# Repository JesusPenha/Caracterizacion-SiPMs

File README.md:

Este repositorio contiene los archivos y los codigos utilizados para la caracterización de los fotomultiplicadores de silicio S133601350CS de hamamatsu.

-La carpeta FotonEquivalente contiene los codigos para el cálculo del equivalente en voltaje de un fotón (p.e) y una gráfica de la función de densidad de probabilidad (PDF) para un conjunto de 10.000 eventos.

-La carpeta Ganancia contiene los codigos para realizar la gráfica de la dependencia de la ganancia en función del sobre voltaje (OV) y de la temperatura (T), asi como los histogramas de carga respectivos.

-En la carpeta Modulos se encuentran los diseños de los circuitos impresos (Eagle) utilizados para cada módulo desarrollado así como los codigos (Arduino) relacionados con el control de temperatura y el medidor de corriente. Adicionalmente contiene la descripcion de Hardware en VHDL para la FPGA utilizada para el módulo de generación de pulsos realizado en ISE design suite- Xilinx.

-La carpeta Ruido están los codigos utilizados para obtener el ruido no correlacionado (DCR) y ruido  correlacionado (afterpulse y crosstalk). 

-La carpeta Voltaje_ruptura contiene los datos de la corrtiente oscura y voltaje de polarización para el SiPM a diferentes temperaturas y el script BreakdownV.ipynb permite obtener la relación entre el voltaje de ruptura y la temperatura a partir de los archivos almacenados en la cerpeta 1350CS.

-El script Data_Record.py es el utilizado por el DAQ (Red pitaya) para el registro y almacenamieto de los eventos (pulsos) en el SiPM.

-El archivo Registro_SiPM.xlsx contiene los registros de voltaje de operacion y corriente oscura a 25°C para 134 SiPMs S13360-1350CS de Hamamatsu.

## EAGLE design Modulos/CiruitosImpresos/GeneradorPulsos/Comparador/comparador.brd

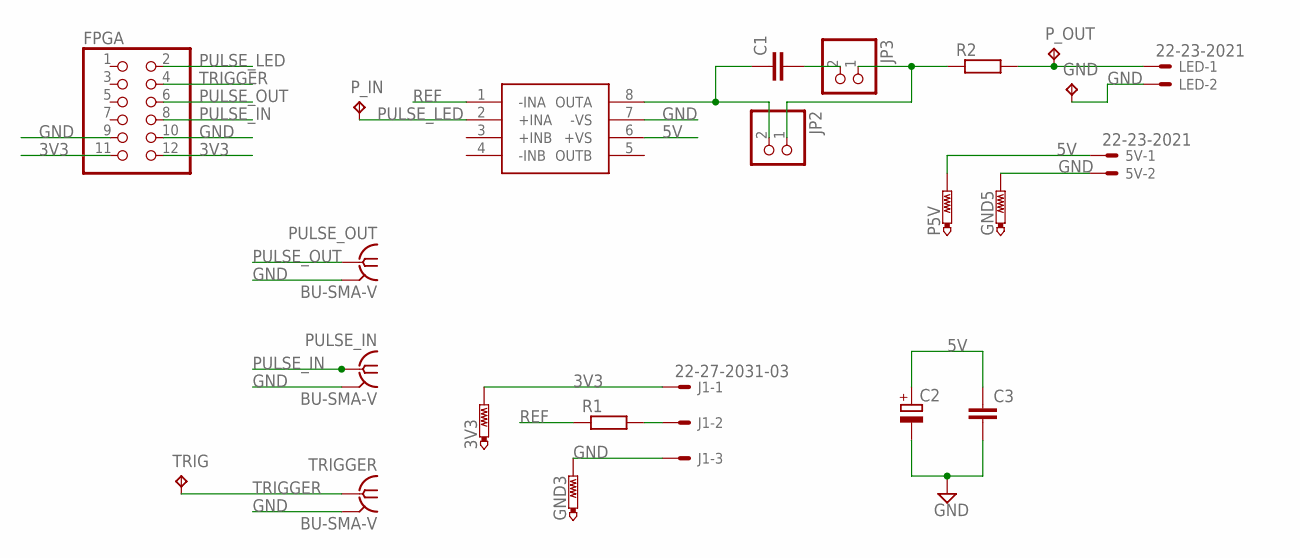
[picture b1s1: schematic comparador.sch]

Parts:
3V3: PTR1TP20SQ; TP20SQ
5V: 22-23-2021
C1, C3: C-EU025-024X044; C025-024X044
C2: CPOL-EUE5-8.5; E5-8,5
FPGA: PINHD-2X6; 2X06
GND: TPPAD1-20; P1-20
GND3, GND5: PTR1TP20SQ; TP20SQ
J1: 22-27-2031-03; 6410-03
JP2, JP3: PINHD-1X2; 1X02
LED: 22-23-2021
OPA: OPA2695; SOIC127P600X175-8N
P5V: PTR1TP20SQ; TP20SQ
PULSE_IN: BU-SMA-V
PULSE_OUT: BU-SMA-V
P_IN: TPPAD1-20; P1-20
P_OUT: TPPAD1-20; P1-20
R1, R2: R-EU_0207/7; 0207/7
TRIG: TPPAD1-20; P1-20
TRIGGER: BU-SMA-V

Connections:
3V3: 3V3.TP, FPGA.11, FPGA.12, J1.1
5V: 5V.1, C2.+, C3.1, OPA.6 (+VS), P5V.TP
GND: 5V.2, C2.-, C3.2, FPGA.9, FPGA.10, GND.TP, GND3.TP, GND5.TP, J1.3, LED.2, OPA.7 (-VS), PULSE_IN.2, PULSE_IN.3 (2), PULSE_IN.4 (2), PULSE_IN.5 (2), PULSE_OUT.2, PULSE_OUT.3 (2), PULSE_OUT.4 (2), PULSE_OUT.5 (2), TRIGGER.2, TRIGGER.3 (2), TRIGGER.4 (2), TRIGGER.5 (2)
unnamed: LED.1, P_OUT.TP, R2.2
unnamed: C1.2, JP3.2
unnamed: C1.1, JP2.2, OPA.8 (OUTA)
unnamed: JP2.1, JP3.1, R2.1
unnamed: J1.2, R1.2
PULSE_IN: FPGA.8, PULSE_IN.1
PULSE_LED: FPGA.2, OPA.2 (+INA), P_IN.TP
PULSE_OUT: FPGA.6, PULSE_OUT.1
REF: OPA.1 (-INA), R1.1
TRIGGER: FPGA.4, TRIG.TP, TRIGGER.1

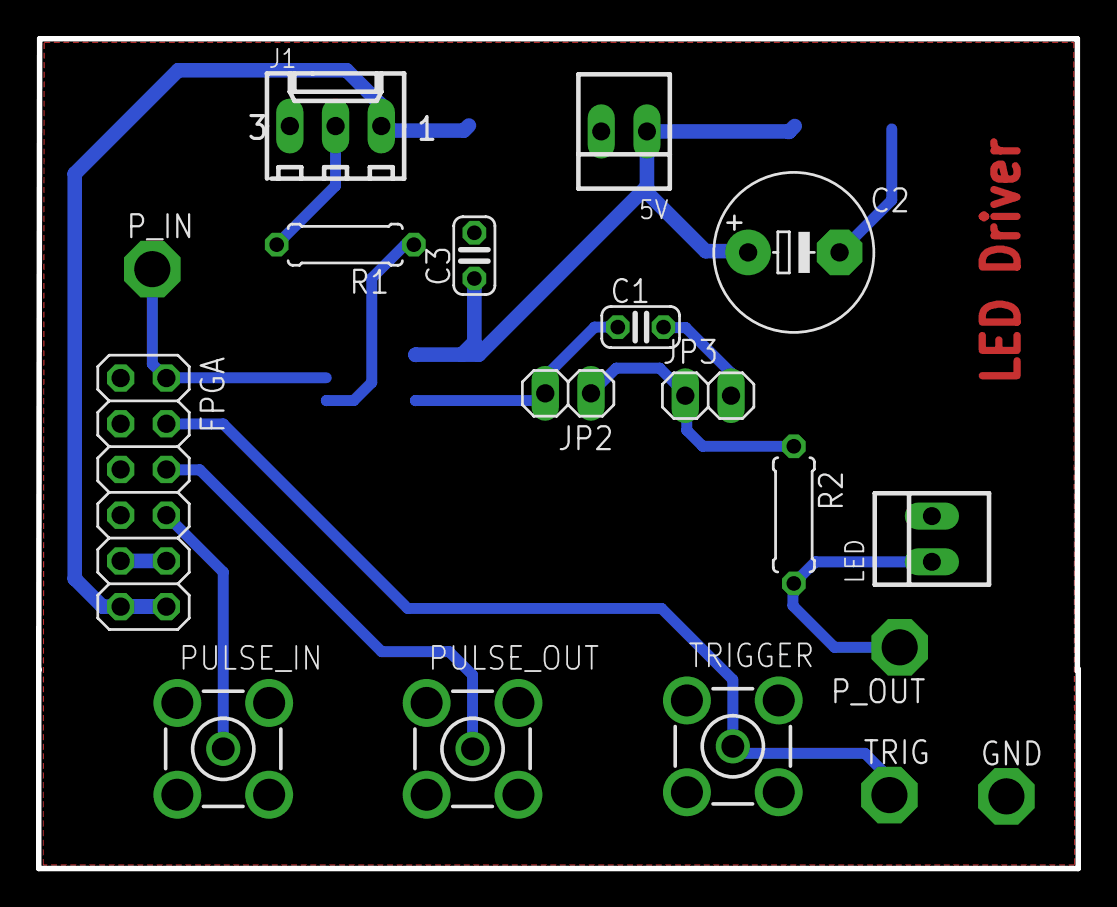
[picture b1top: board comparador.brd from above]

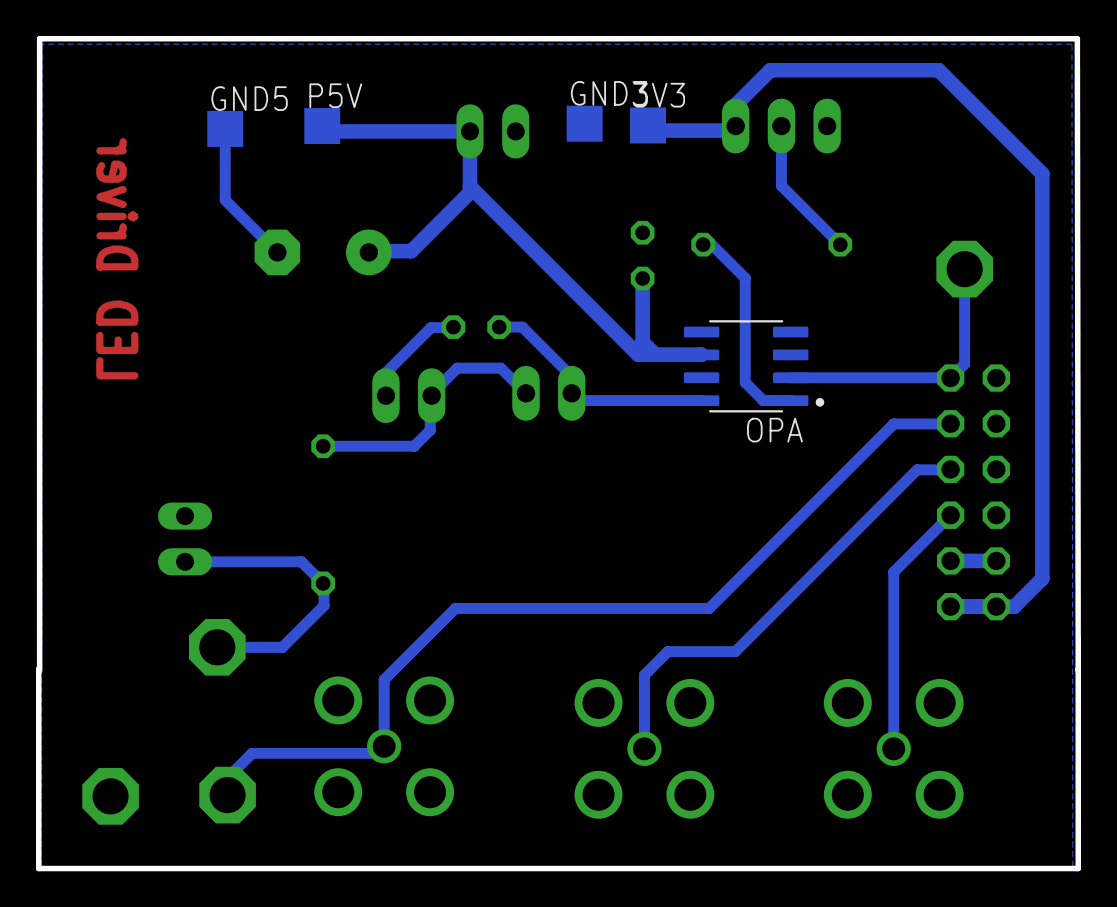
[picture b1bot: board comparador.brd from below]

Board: 2 copper layers, 57.8 x 46.1 mm, 23 parts (5 on the bottom side), 13 nets.

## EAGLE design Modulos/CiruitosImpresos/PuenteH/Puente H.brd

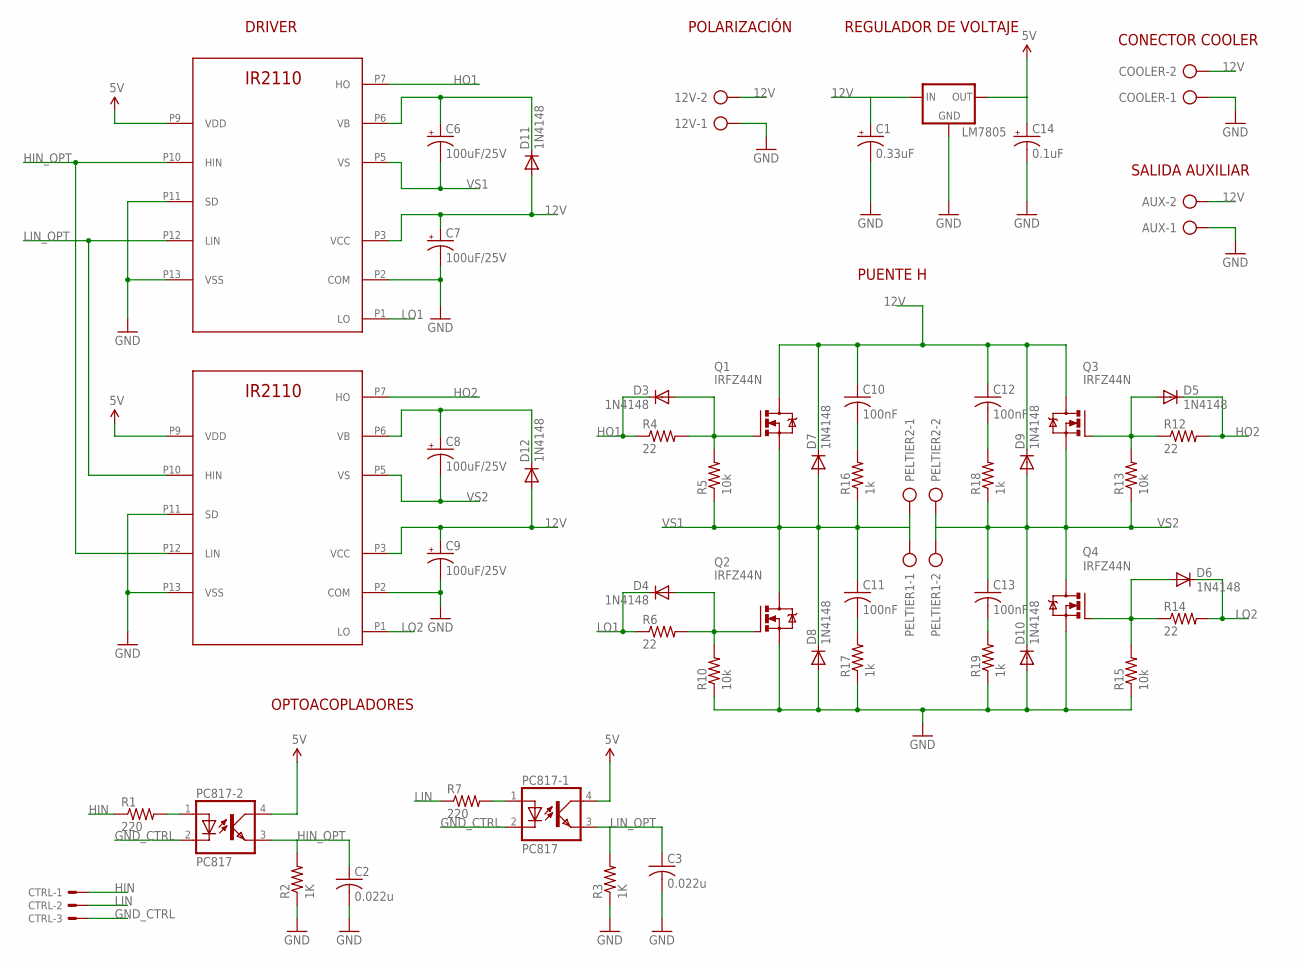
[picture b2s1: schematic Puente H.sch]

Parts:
12V: AK500/2
AUX: AK500/2
C1: 0.33uF; E2,5-6
C2, C3: 0.022u; C102-043X133
C6, C7, C8, C9: 100uF/25V; E2,5-7
C10, C11, C12, C13: 100nF; C025-025X050
C14: 0.1uF; E2,5-6
COOLER: AK500/2
CTRL: 22-23-2031
D3, D4, D5, D6, D7, D8, D9, D10, D11, D12: 1N4148; DIODE-1N4148
IR2110-1, IR2110-2: IR2110N; DIL14-1
LM7805: 78XXS
PC817-1, PC817-2: PC817; DIL04
PELTIER1, PELTIER2: AK500/2
Q1, Q2, Q3, Q4: IRFZ44N; TO220BV
R1, R7: 220; 0207/10
R2, R3: 1K; 0207/10
R4, R6, R12, R14: 22; 0207/10
R5, R10, R13, R15: 10k; 0207/10
R16, R17, R18, R19: 1k; 0207/10

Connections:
5V: C14.+, IR2110-1.P9 (VDD), IR2110-2.P9 (VDD), LM7805.OUT, PC817-1.4 (COL), PC817-2.4 (COL)
12V: 12V.2, AUX.2, C1.+, C7.+, C9.+, C10.1, C12.1, COOLER.2, D7.C, D9.C, D11.A, D12.A, IR2110-1.P3 (VCC), IR2110-2.P3 (VCC), LM7805.IN, Q1.D, Q3.D
GND: 12V.1, AUX.1, C1.-, C2.2, C3.2, C7.-, C9.-, C14.-, COOLER.1, D8.A, D10.A, IR2110-1.P2 (COM), IR2110-1.P11 (SD), IR2110-1.P13 (VSS), IR2110-2.P2 (COM), IR2110-2.P11 (SD), IR2110-2.P13 (VSS), LM7805.GND, Q2.S, Q4.S, R2.1, R3.1, R10.1, R15.1, R17.1, R19.1
GND_CTRL: CTRL.3, PC817-1.2 (C), PC817-2.2 (C)
HIN: CTRL.1, R1.1
HIN_OPT: C2.1, IR2110-1.P10 (HIN), IR2110-2.P12 (LIN), PC817-2.3 (EMIT), R2.2
HO1: D3.C, IR2110-1.P7 (HO), R4.1
HO2: D5.C, IR2110-2.P7 (HO), R12.2
LIN: CTRL.2, R7.1
LIN_OPT: C3.1, IR2110-1.P12 (LIN), IR2110-2.P10 (HIN), PC817-1.3 (EMIT), R3.2
LO1: D4.C, IR2110-1.P1 (LO), R6.1
LO2: D6.C, IR2110-2.P1 (LO), R14.2
unnamed: PC817-1.1 (A), R7.2
unnamed: PC817-2.1 (A), R1.2
unnamed: D5.A, Q3.G, R12.1, R13.2
unnamed: C6.+, D11.C, IR2110-1.P6 (VB)
unnamed: D3.A, Q1.G, R4.2, R5.2
unnamed: D4.A, Q2.G, R6.2, R10.2
unnamed: D6.A, Q4.G, R14.1, R15.2
unnamed: C12.2, R18.2
unnamed: C10.2, R16.2
unnamed: C13.2, R19.2
unnamed: C11.2, R17.2
unnamed: C8.+, D12.C, IR2110-2.P6 (VB)
VS1: C6.-, C11.1, D7.A, D8.C, IR2110-1.P5 (VS), PELTIER1.1, PELTIER2.1, Q1.S, Q2.D, R5.1, R16.1
VS2: C8.-, C13.1, D9.A, D10.C, IR2110-2.P5 (VS), PELTIER1.2, PELTIER2.2, Q3.S, Q4.D, R13.1, R18.1

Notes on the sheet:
OPTOACOPLADORES
PUENTE H
SALIDA AUXILIAR
CONECTOR COOLER
REGULADOR DE VOLTAJE
POLARIZACIÓN
DRIVER

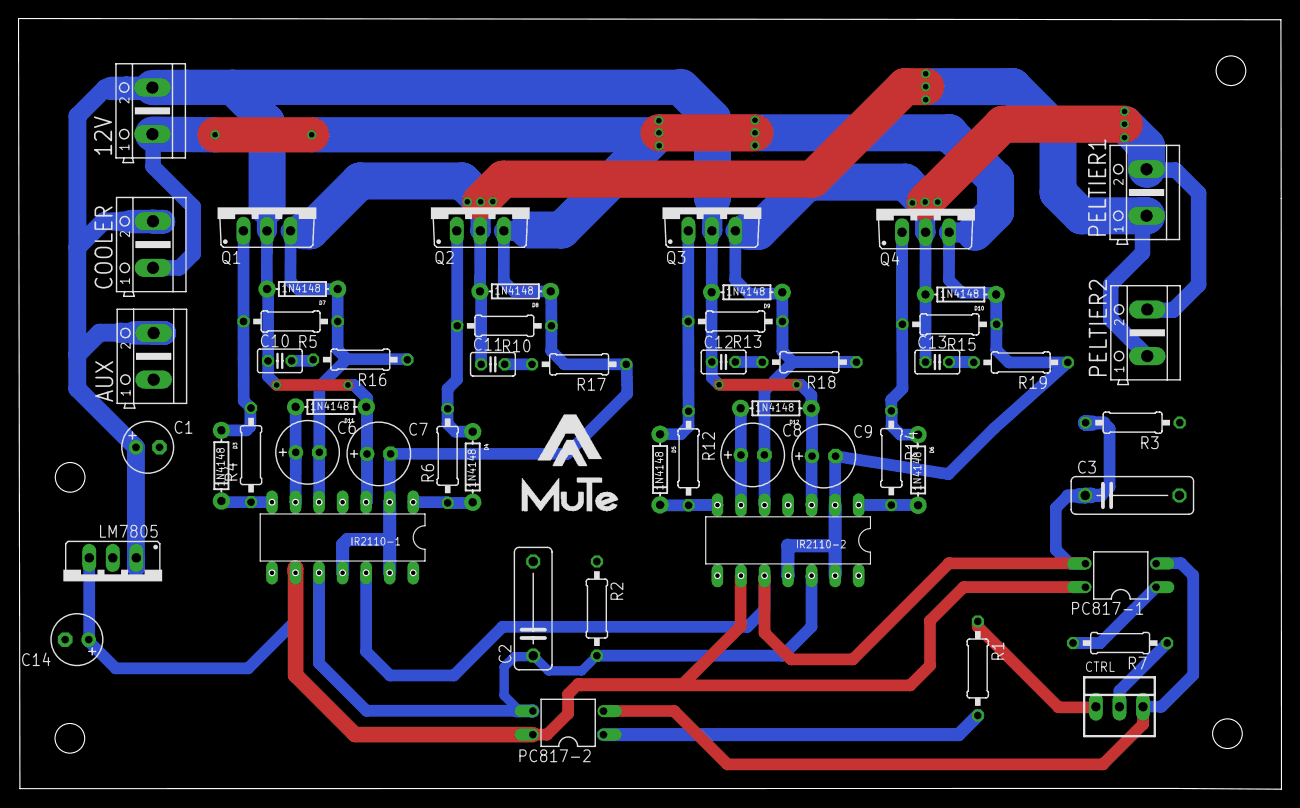
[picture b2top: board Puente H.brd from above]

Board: 2 copper layers, 136.3 x 83.2 mm, 53 parts (0 on the bottom side), 26 nets.

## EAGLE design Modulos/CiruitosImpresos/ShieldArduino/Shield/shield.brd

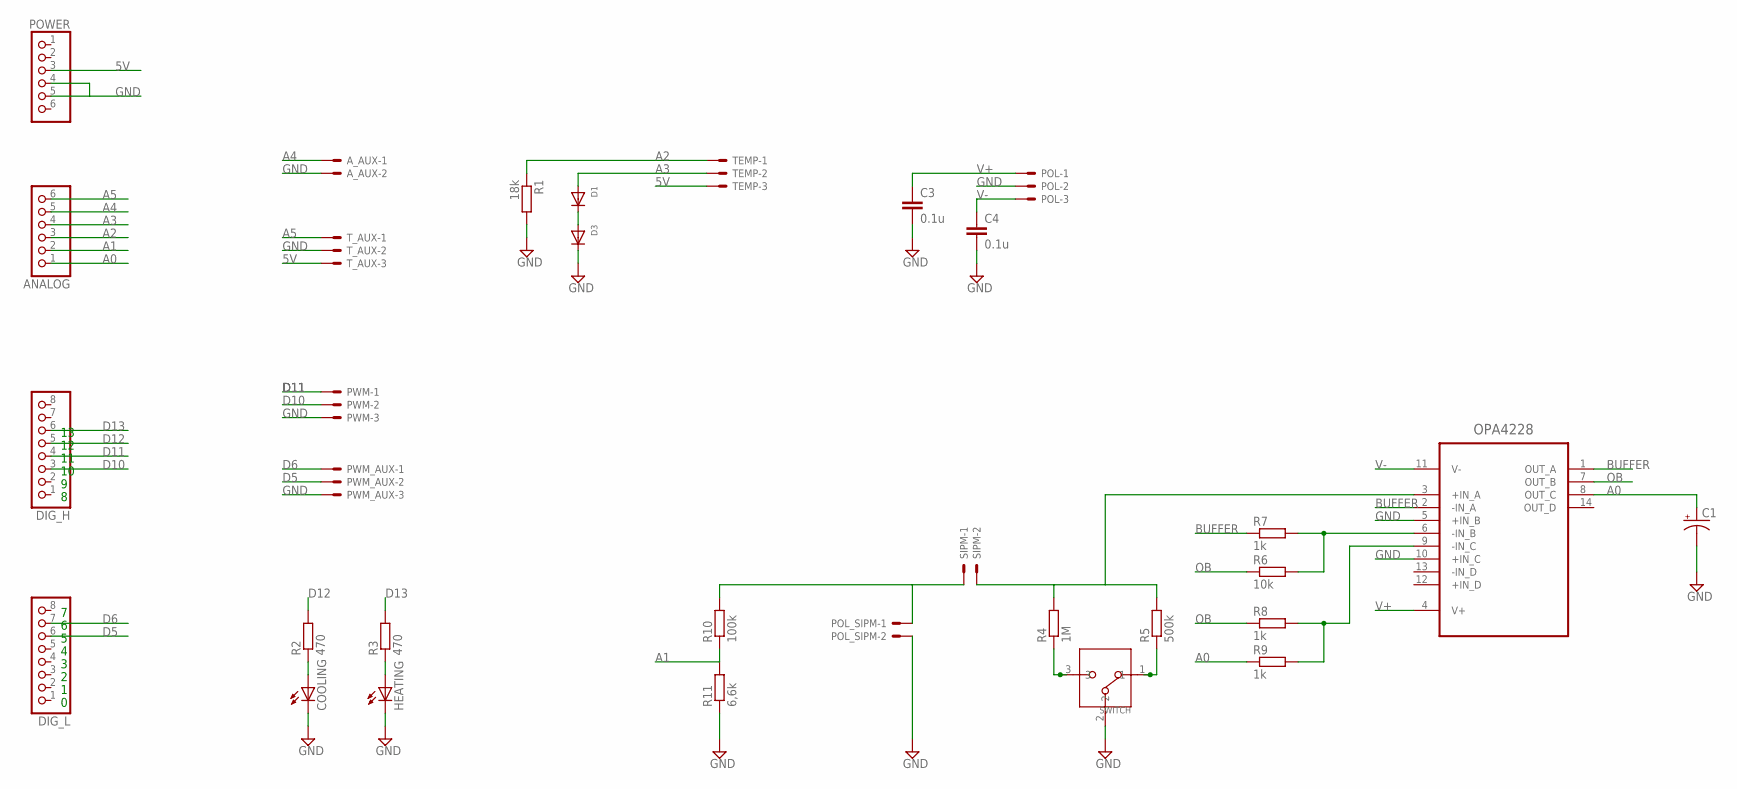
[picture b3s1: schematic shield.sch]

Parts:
ANALOG: PINHD-1X6; 1X06
A_AUX: 22-23-2021
C1: CPOL-USSMCC; SMC_C
C3, C4: 0.1u; C0805K
COOLING: LEDSMT1206; 1206
D1, D3: DIODEDO-1N4148; DO-1N4148
DIG_H: PINHD-1X8; 1X08
DIG_L: PINHD-1X8; 1X08
HEATING: LEDSMT1206; 1206
OPA4228: OPA4228UA; SOIC127P600X175-14N
POL: 22-23-2031
POL_SIPM: 22-23-2021
POWER: PINHD-1X6; 1X06
PWM: 22-23-2031
PWM_AUX: 22-23-2031
R1: 18k; 0309/12
R2, R3: 470; R0805W
R4: 1M; R0805W
R5: 500k; R0805W
R6: 10k; R0805W
R7, R8, R9: 1k; R0805W
R10: 100k; R0805W
R11: 6,6k; R0805W
SIPM: 22-23-2021
SWITCH: DIP-SLIDE-SWITCH(3P-11.6X4.0X5.4+2.0MM)-EG1218; SW3-2.5-11.6X4.0X5.4+2.0MM
TEMP: 22-23-2031
T_AUX: 22-23-2031

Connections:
5V: POWER.3, TEMP.3, T_AUX.3
A0: ANALOG.1, C1.+, OPA4228.8 (OUT_C), R9.1
A1: ANALOG.2, R10.1, R11.2
A2: ANALOG.3, R1.1, TEMP.1
A3: ANALOG.4, D1.A, TEMP.2
A4: ANALOG.5, A_AUX.1
A5: ANALOG.6, T_AUX.1
BUFFER: OPA4228.1 (OUT_A), OPA4228.2 (-IN_A), R7.1
D5: DIG_L.6, PWM_AUX.2
D6: DIG_L.7, PWM_AUX.1
D10: DIG_H.3, PWM.2
D11: DIG_H.4, PWM.1
D12: DIG_H.5, R2.2
D13: DIG_H.6, R3.2
GND: A_AUX.2, C1.-, C3.2, C4.2, COOLING.C, D3.C, HEATING.C, OPA4228.5 (+IN_B), OPA4228.10 (+IN_C), POL.2, POL_SIPM.2, POWER.4, POWER.5, PWM.3, PWM_AUX.3, R1.2, R11.1, SWITCH.2, T_AUX.2
unnamed: COOLING.A, R2.1
unnamed: HEATING.A, R3.1
unnamed: OPA4228.6 (-IN_B), R6.2, R7.2
unnamed: POL_SIPM.1, R10.2, SIPM.1
unnamed: R4.1, SWITCH.3
unnamed: R5.1, SWITCH.1
unnamed: OPA4228.3 (+IN_A), R4.2, R5.2, SIPM.2
unnamed: OPA4228.9 (-IN_C), R8.2, R9.2
unnamed: D1.C, D3.A
OB: OPA4228.7 (OUT_B), R6.1, R8.1
V+: C3.1, OPA4228.4 (V+), POL.1
V-: C4.1, OPA4228.11 (V-), POL.3

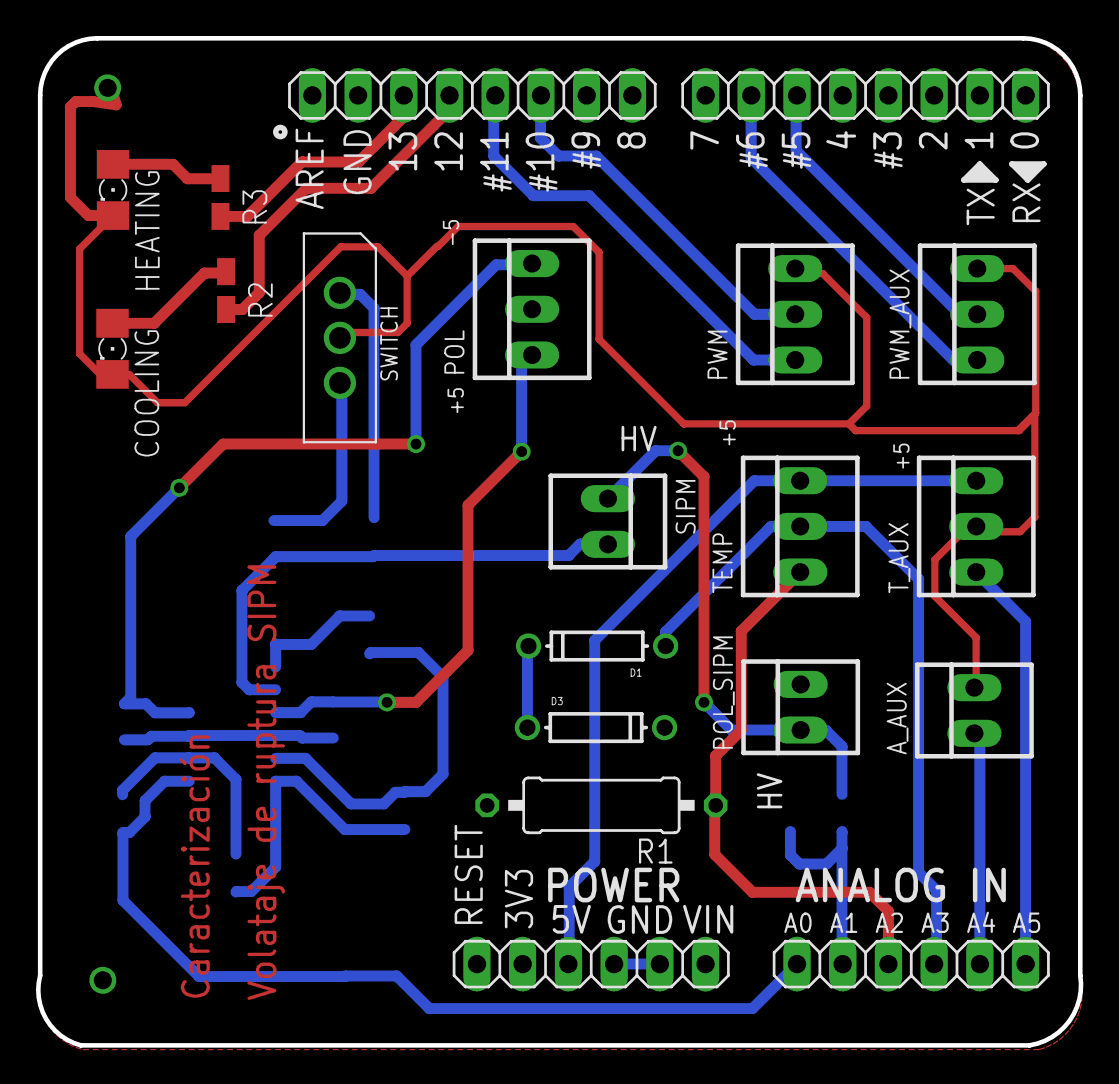
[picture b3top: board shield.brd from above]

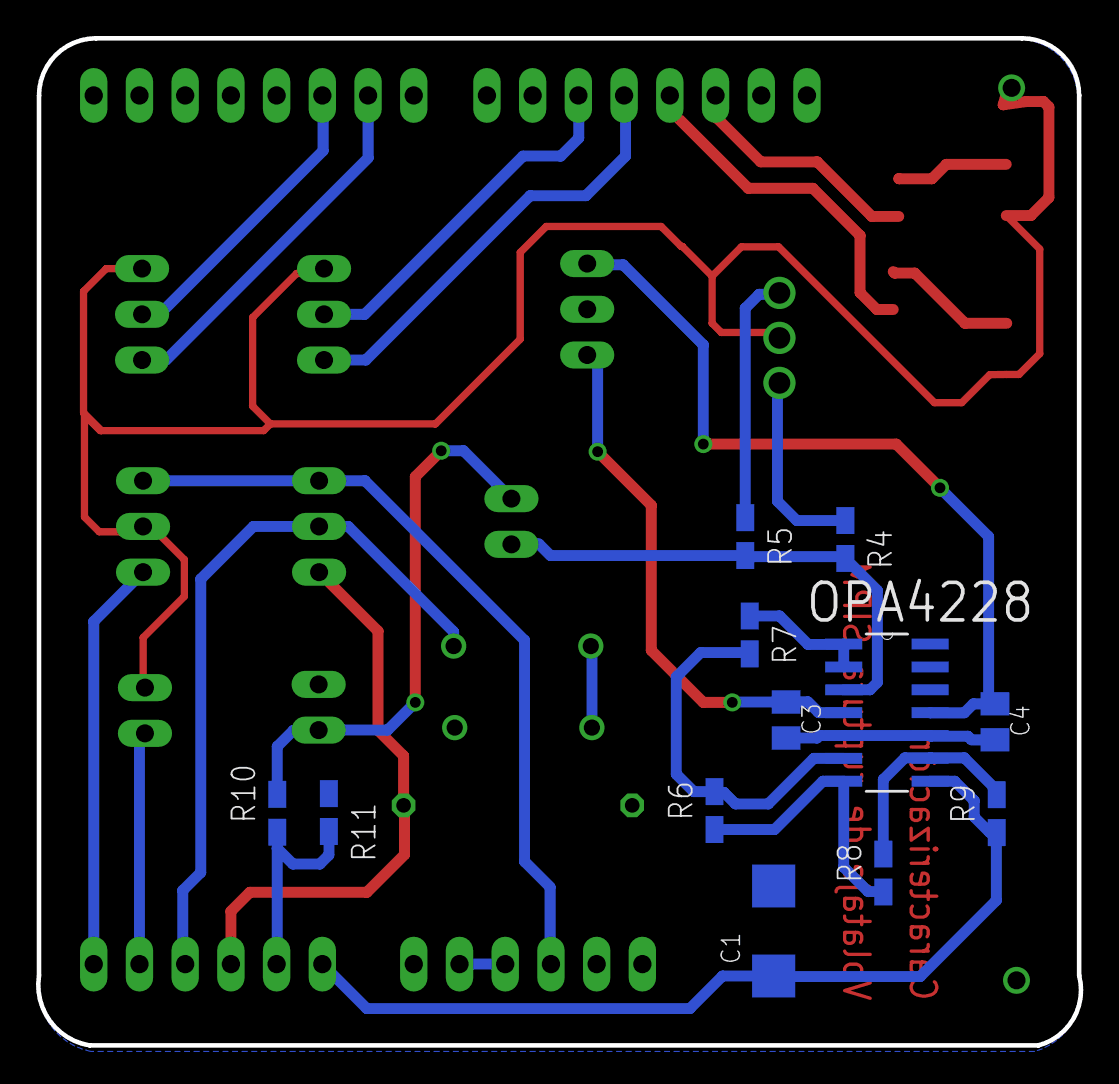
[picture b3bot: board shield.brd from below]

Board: 2 copper layers, 57.9 x 55.9 mm, 32 parts (12 on the bottom side), 27 nets.

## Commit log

2020-03-03 Rename FotonEquivalente/Histogramas_1350CS-_CDF.ipynb to PDF_1350CS.ipynb
2020-03-03 Rename Histogramas_1350CS-_CDF.ipynb to PDF_1350CS.ipynb
2020-03-03 Rename Ruido/After_Cross_1350CS.ipynb to 1350CS_Noise_vs_OV.ipynb
2020-03-03 Rename 1350CS_Noise_vs_OV.ipynb to Ruido/1350CS_Noise_vs_OV.ipynb
2020-03-03 Rename After_Cross_1350CS-Copy1.ipynb to 1350CS_Noise_vs_T.ipynb

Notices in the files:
parts and their libraries:
SparkFun: Licensing: CC v3.0 Share-Alike You are welcome to use this library for commercial purposes.
